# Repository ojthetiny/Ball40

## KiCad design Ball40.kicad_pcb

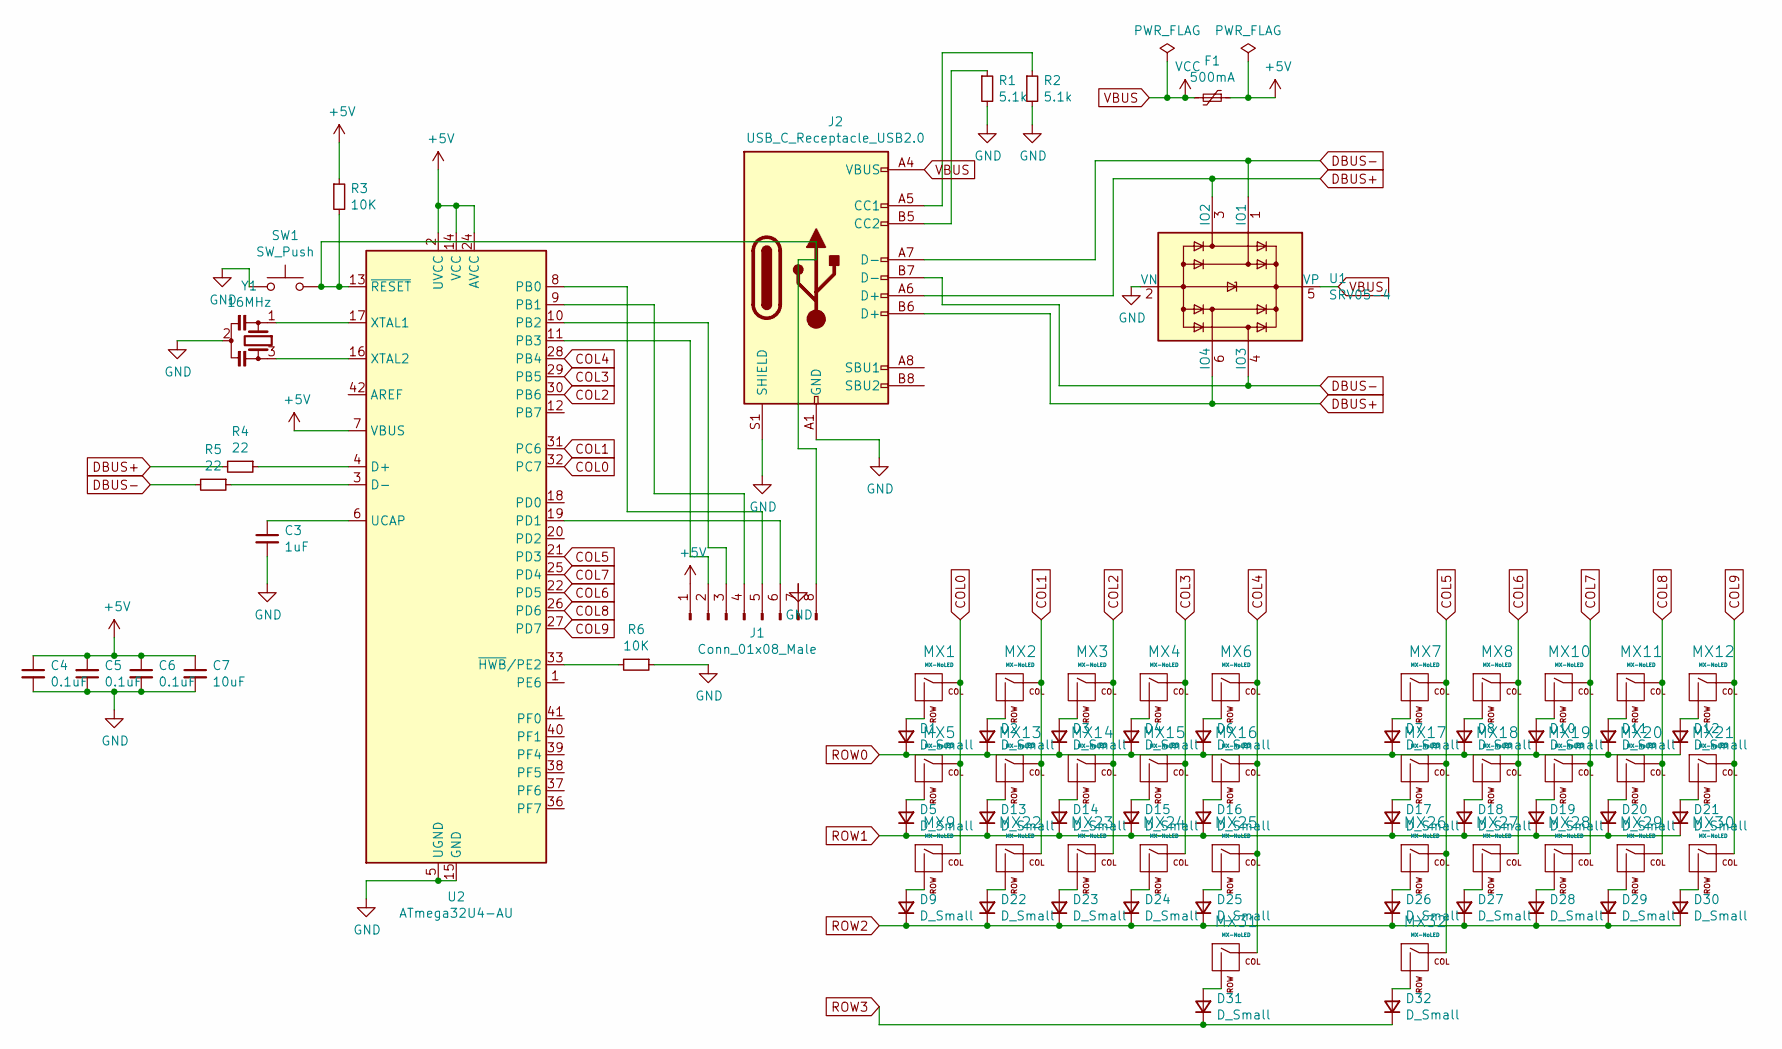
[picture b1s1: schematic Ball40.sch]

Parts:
C3: 1uF; C_0805_2012Metric; LCSC C28323
C4, C5, C6: 0.1uF; C_0402_1005Metric; LCSC C24497
C7: 10uF; C_0805_2012Metric; LCSC C15850
D1, D2, D3, D4, D5, D6, D7, D8, D9, D10, D11, D12, D13, D14, D15, D16, D17, D18, D19, D20, D21, D22, D23, D24, D25, D26, D27, D28, D29, D30, D31, D32: D_Small; D_SOD-123; LCSC C81598
F1: 500mA; Fuse_1206_3216Metric; LCSC C206993
J1: Conn_01x08_Male; JST_SH_SM08B-SRSS-TB_1x08-1MP_P1.00mm_Horizontal
J2: USB_C_Receptacle_USB2.0; USB_C_GCT_USB4085
MX1, MX2, MX3, MX4, MX5, MX6, MX7, MX8, MX9, MX10, MX11, MX12, MX13, MX14, MX15, MX16, MX17, MX18, MX19, MX20, MX21, MX22, MX23, MX24, MX25, MX26, MX27, MX28, MX29, MX30: MX-NoLED; SW_Cherry_MX_1.00u_PCB
MX31, MX32: MX-NoLED; MXOnly-2.25U-ReversedStabilizers-NoLED
R1, R2: 5.1k; R_0805_2012Metric; LCSC C27834
R3, R6: 10K; R_0805_2012Metric; LCSC C17414
R4, R5: 22; R_0805_2012Metric; LCSC C17561
SW1: SW_Push; SKQG-1155865; LCSC C318884
U1: SRV05-4; SOT-23-6; LCSC C384887
U2: ATmega32U4-AU; TQFP-44_10x10mm_P0.8mm; LCSC C44854
Y1: 16MHz; Resonator_SMD_muRata_CSTxExxV-3Pin_3.0x1.1mm; LCSC C13738

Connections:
+5V: C4.1, C5.2, C6.1, C7.1, F1.1, J1.1, R3.1, U2.2 (UVCC), U2.7 (VBUS), U2.14 (VCC), U2.24 (AVCC), U2.34 (VCC), U2.44 (AVCC)
COL0: MX1.1 (COL), MX5.1 (COL), MX9.1 (COL), U2.32 (PC7)
COL1: MX2.1 (COL), MX13.1 (COL), MX22.1 (COL), U2.31 (PC6)
COL2: MX3.1 (COL), MX14.1 (COL), MX23.1 (COL), U2.30 (PB6)
COL3: MX4.1 (COL), MX15.1 (COL), MX24.1 (COL), U2.29 (PB5)
COL4: MX6.1 (COL), MX16.1 (COL), MX25.1 (COL), MX31.1 (COL), U2.28 (PB4)
COL5: MX7.1 (COL), MX17.1 (COL), MX26.1 (COL), MX32.1 (COL), U2.21 (PD3)
COL6: MX8.1 (COL), MX18.1 (COL), MX27.1 (COL), U2.22 (PD5)
COL7: MX10.1 (COL), MX19.1 (COL), MX28.1 (COL), U2.25 (PD4)
COL8: MX11.1 (COL), MX20.1 (COL), MX29.1 (COL), U2.26 (PD6)
COL9: MX12.1 (COL), MX21.1 (COL), MX30.1 (COL), U2.27 (PD7)
DBUS+: J2.A6 (D+), J2.B6 (D+), R4.2, U1.3 (IO2), U1.6 (IO4)
DBUS-: J2.A7 (D-), J2.B7 (D-), R5.2, U1.1 (IO1), U1.4 (IO3)
GND: C3.2, C4.2, C5.1, C6.2, C7.2, J1.7, J2.A1 (GND), J2.A12 (GND), J2.B1 (GND), J2.B12 (GND), J2.S1 (SHIELD), R1.2, R2.2, R6.1, SW1.1, U1.2 (VN), U2.5 (UGND), U2.15 (GND), U2.23 (GND), U2.35 (GND), U2.43 (GND), Y1.2
unnamed: C3.1, U2.6 (UCAP)
unnamed: D1.2 (A), MX1.2 (ROW)
unnamed: D2.2 (A), MX2.2 (ROW)
unnamed: D3.2 (A), MX3.2 (ROW)
unnamed: D4.2 (A), MX4.2 (ROW)
unnamed: D5.2 (A), MX5.2 (ROW)
unnamed: D6.2 (A), MX6.2 (ROW)
unnamed: D7.2 (A), MX7.2 (ROW)
unnamed: D8.2 (A), MX8.2 (ROW)
unnamed: D9.2 (A), MX9.2 (ROW)
unnamed: D10.2 (A), MX10.2 (ROW)
unnamed: D11.2 (A), MX11.2 (ROW)
unnamed: D12.2 (A), MX12.2 (ROW)
unnamed: D13.2 (A), MX13.2 (ROW)
unnamed: D14.2 (A), MX14.2 (ROW)
unnamed: D15.2 (A), MX15.2 (ROW)
unnamed: D16.2 (A), MX16.2 (ROW)
unnamed: D17.2 (A), MX17.2 (ROW)
unnamed: D18.2 (A), MX18.2 (ROW)
unnamed: D19.2 (A), MX19.2 (ROW)
unnamed: D20.2 (A), MX20.2 (ROW)
unnamed: D21.2 (A), MX21.2 (ROW)
unnamed: D22.2 (A), MX22.2 (ROW)
unnamed: D23.2 (A), MX23.2 (ROW)
unnamed: D24.2 (A), MX24.2 (ROW)
unnamed: D25.2 (A), MX25.2 (ROW)
unnamed: D26.2 (A), MX26.2 (ROW)
unnamed: D27.2 (A), MX27.2 (ROW)
unnamed: D28.2 (A), MX28.2 (ROW)
unnamed: D29.2 (A), MX29.2 (ROW)
unnamed: D30.2 (A), MX30.2 (ROW)
unnamed: D31.2 (A), MX31.2 (ROW)
unnamed: D32.2 (A), MX32.2 (ROW)
unnamed: J1.2, U2.11 (PB3)
unnamed: J1.3, U2.10 (PB2)
unnamed: J1.4, U2.9 (PB1)
unnamed: J1.5, U2.8 (PB0)
unnamed: J1.6, U2.19 (PD1)
unnamed: J1.8, R3.2, SW1.2, U2.13 (~RESET)
unnamed: J2.A5 (CC1), R2.1
unnamed: J2.B5 (CC2), R1.1
unnamed: R4.1, U2.4 (D+)
unnamed: R5.1, U2.3 (D-)
unnamed: R6.2, U2.33 (~HWB~/PE2)
unnamed: U2.16 (XTAL2), Y1.3
unnamed: U2.17 (XTAL1), Y1.1
ROW0: D1.1 (K), D2.1 (K), D3.1 (K), D4.1 (K), D6.1 (K), D7.1 (K), D8.1 (K), D10.1 (K), D11.1 (K), D12.1 (K)
ROW1: D5.1 (K), D13.1 (K), D14.1 (K), D15.1 (K), D16.1 (K), D17.1 (K), D18.1 (K), D19.1 (K), D20.1 (K), D21.1 (K)
ROW2: D9.1 (K), D22.1 (K), D23.1 (K), D24.1 (K), D25.1 (K), D26.1 (K), D27.1 (K), D28.1 (K), D29.1 (K), D30.1 (K)
ROW3: D31.1 (K), D32.1 (K)
VBUS: F1.2, J2.A4 (VBUS), J2.A9 (VBUS), J2.B4 (VBUS), J2.B9 (VBUS), U1.5 (VP)

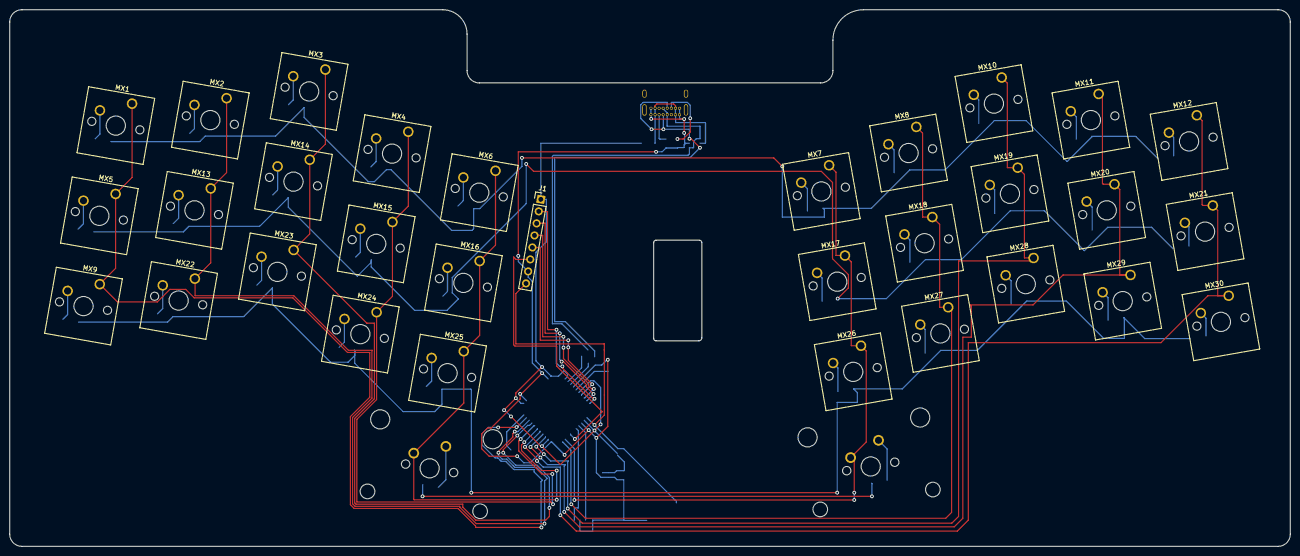
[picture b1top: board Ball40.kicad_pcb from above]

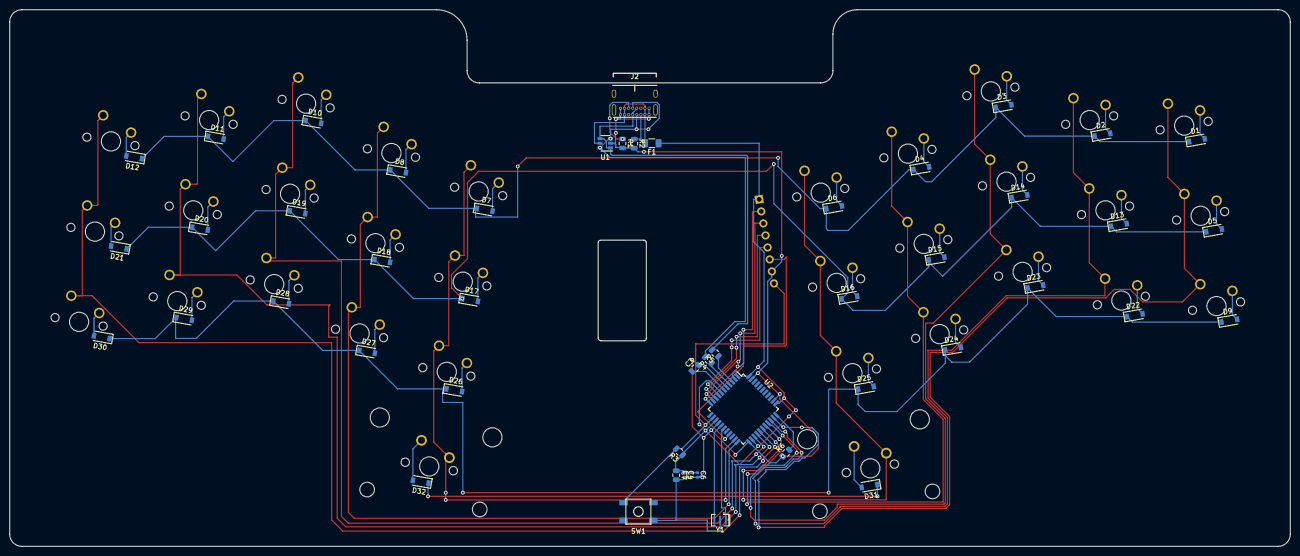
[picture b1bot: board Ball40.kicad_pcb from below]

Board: 2 copper layers, 266.7 x 111.8 mm, 82 parts (49 on the bottom side), 65 nets.

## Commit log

2020-09-15 Inital commit
2020-09-15 added submodules
2020-09-15 Completed PCB schematic and footprinting
2020-09-17 placed components in the PCB file
2020-09-20 generated gerbers
